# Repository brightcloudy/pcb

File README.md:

# pcb
Some OSHW PCBs that I have designed/am designing.

* zipscripts - Scripts built to zip up KiCad gerbers for tools such as gerblook.

* vna-steps - Boards designed to step up in complexity towards the modules required for the full 1 GHz VNA.
  * slowdds - AD9833 + STM32F030 based DDS module requiring external UART adapter.

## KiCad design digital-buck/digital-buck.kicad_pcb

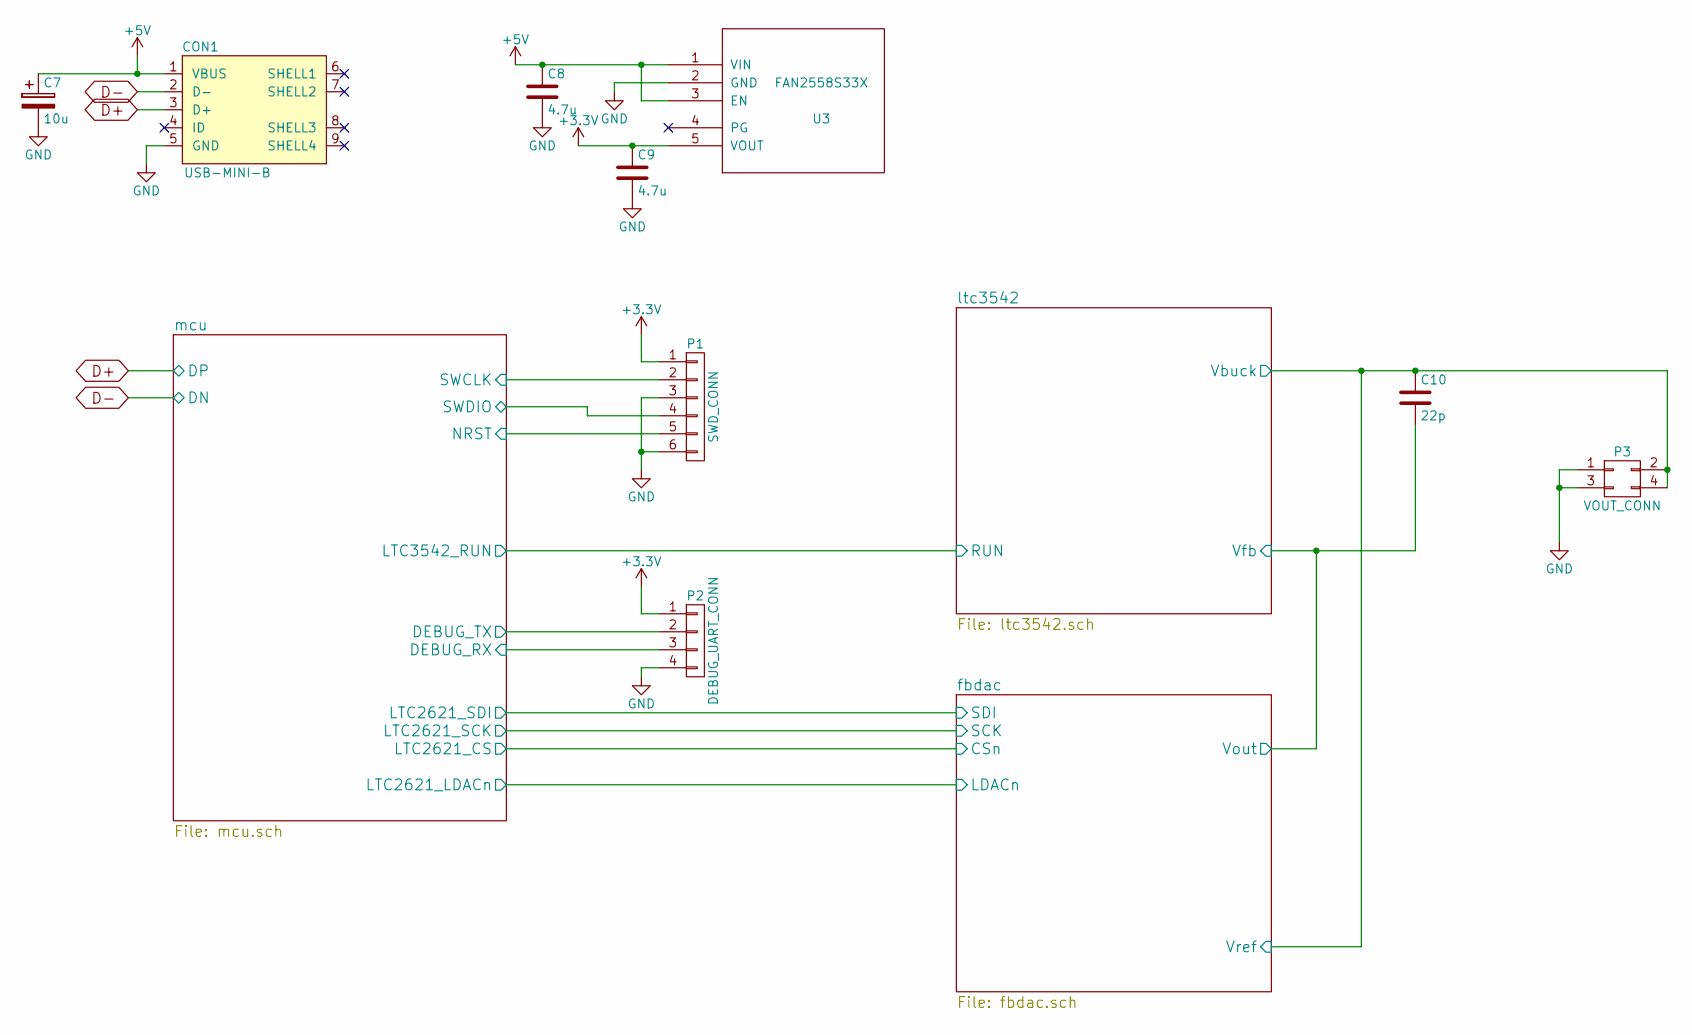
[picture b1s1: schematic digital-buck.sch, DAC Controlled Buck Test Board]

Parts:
C7: 10u; TantalC_SizeA_EIA-3216_Reflow
C8, C9: 4.7u; C_0603
C10: 22p; C_0603
CON1: USB-MINI-B; USB_Mini-B
P1: SWD_CONN; Pin_Header_Straight_1x06
P2: DEBUG_UART_CONN; Pin_Header_Straight_1x04
P3: VOUT_CONN; Pin_Header_Straight_2x02
U3: FAN2558S33X; SOT-23-5

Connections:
+3V3: C9.1, P1.1, P2.1, U3.5 (VOUT); also elsewhere on the board
+5V: C7.1, C8.1, CON1.1 (VBUS), U3.1 (VIN), U3.3 (EN); also elsewhere on the board
/ltc3542/Vbuck: C10.1, P3.2, P3.4; also elsewhere on the board
/ltc3542/Vfb: C10.2; also elsewhere on the board
/mcu/DEBUG_RX: P2.3; also elsewhere on the board
/mcu/DEBUG_TX: P2.2; also elsewhere on the board
/mcu/NRST: P1.5; also elsewhere on the board
/mcu/SWCLK: P1.2; also elsewhere on the board
/mcu/SWDIO: P1.4; also elsewhere on the board
D+: CON1.3 (D+); also elsewhere on the board
D-: CON1.2 (D-); also elsewhere on the board
GND: C7.2, C8.2, C9.2, CON1.5 (GND), P1.3, P1.6, P2.4, P3.1, P3.3, U3.2 (GND); also elsewhere on the board

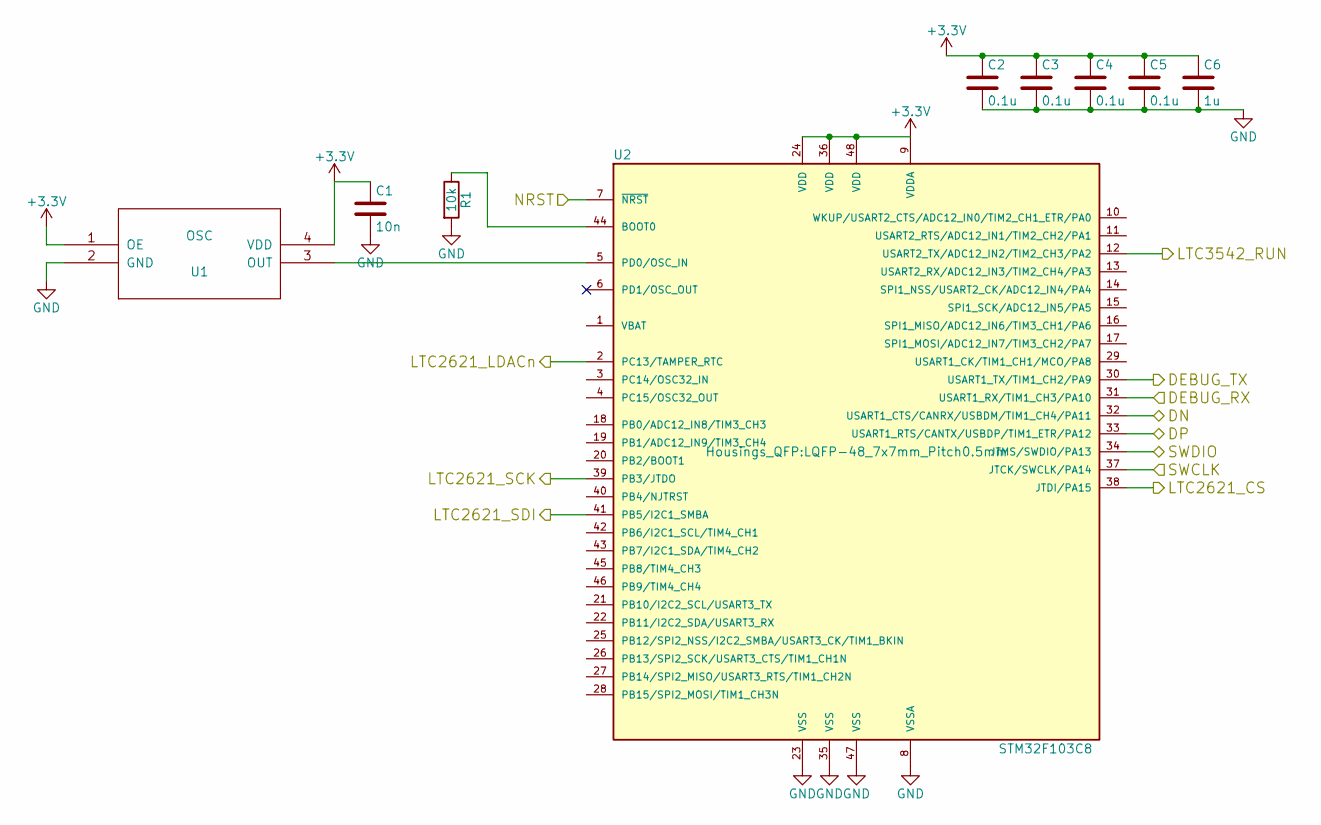
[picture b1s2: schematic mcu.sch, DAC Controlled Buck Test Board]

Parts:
C1: 10n; C_0402
C2, C3, C4, C5: 0.1u; C_0402
C6: 1u; C_0402
R1: 10k; R_0402
U1: OSC; SIOSC
U2: STM32F103C8; LQFP-48_7x7mm_Pitch0.5mm

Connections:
+3V3: C1.1, C2.1, C3.1, C4.1, C5.1, C6.1, U1.1 (OE), U1.4 (VDD), U2.9 (VDDA), U2.24 (VDD), U2.36 (VDD), U2.48 (VDD); also elsewhere on the board
/fbdac/CSn: U2.38 (JTDI/PA15); also elsewhere on the board
/fbdac/LDACn: U2.2 (PC13/TAMPER_RTC); also elsewhere on the board
/mcu/DEBUG_RX: U2.31 (USART1_RX/TIM1_CH3/PA10); also elsewhere on the board
/mcu/DEBUG_TX: U2.30 (USART1_TX/TIM1_CH2/PA9); also elsewhere on the board
/mcu/LTC2621_SCK: U2.39 (PB3/JTDO); also elsewhere on the board
/mcu/LTC2621_SDI: U2.41 (PB5/I2C1_SMBA); also elsewhere on the board
/mcu/LTC3542_RUN: U2.12 (USART2_TX/ADC12_IN2/TIM2_CH3/PA2); also elsewhere on the board
/mcu/NRST: U2.7 (~NRST); also elsewhere on the board
/mcu/SWCLK: U2.37 (JTCK/SWCLK/PA14); also elsewhere on the board
/mcu/SWDIO: U2.34 (JTMS/SWDIO/PA13); also elsewhere on the board
D+: U2.33 (USART1_RTS/CANTX/USBDP/TIM1_ETR/PA12); also elsewhere on the board
D-: U2.32 (USART1_CTS/CANRX/USBDM/TIM1_CH4/PA11); also elsewhere on the board
GND: C1.2, C2.2, C3.2, C4.2, C5.2, C6.2, R1.2, U1.2 (GND), U2.8 (VSSA), U2.23 (VSS), U2.35 (VSS), U2.47 (VSS); also elsewhere on the board
unnamed: R1.1, U2.44 (BOOT0)
unnamed: U1.3 (OUT), U2.5 (PD0/OSC_IN)

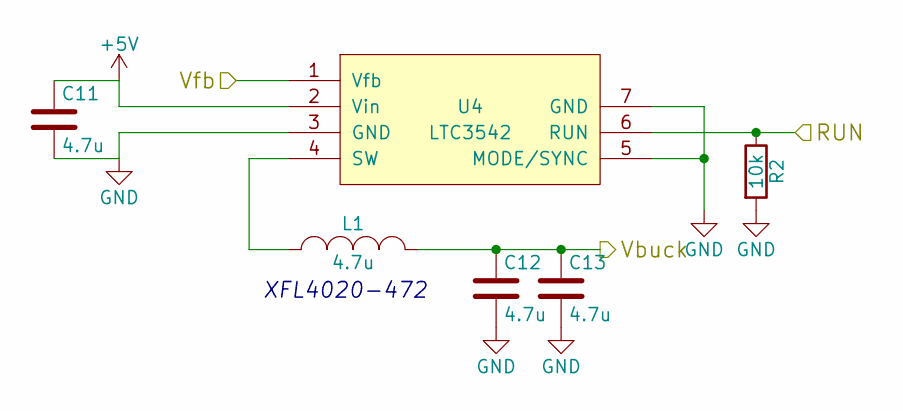
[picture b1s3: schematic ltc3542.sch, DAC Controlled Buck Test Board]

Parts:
C11, C12, C13: 4.7u; C_0603
L1: 4.7u; XFL4020
R2: 10k; R_0402
U4: LTC3542; DFN-6-1EP_2x2mm_Pitch0.5mm

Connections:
+5V: C11.1, U4.2 (Vin); also elsewhere on the board
/ltc3542/Vbuck: C12.1, C13.1, L1.2; also elsewhere on the board
/ltc3542/Vfb: U4.1 (Vfb); also elsewhere on the board
/mcu/LTC3542_RUN: R2.1, U4.6 (RUN); also elsewhere on the board
GND: C11.2, C12.2, C13.2, R2.2, U4.3 (GND), U4.5 (MODE/SYNC), U4.7 (GND); also elsewhere on the board
unnamed: L1.1, U4.4 (SW)

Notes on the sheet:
XFL4020-472

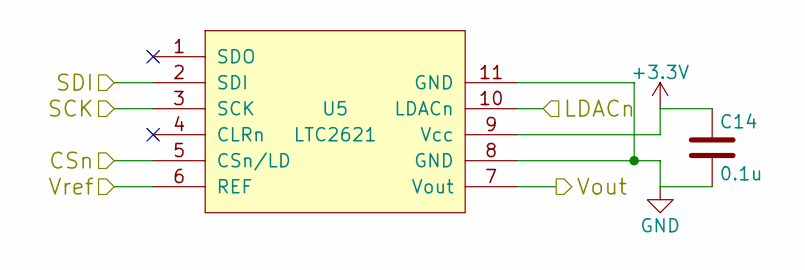
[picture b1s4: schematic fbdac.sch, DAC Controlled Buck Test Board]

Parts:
C14: 0.1u; C_0402
U5: LTC2621; DFN-10-1EP_3x3mm_Pitch0.5mm

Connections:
+3V3: C14.1, U5.9 (Vcc); also elsewhere on the board
/fbdac/CSn: U5.5 (CSn/LD); also elsewhere on the board
/fbdac/LDACn: U5.10 (LDACn); also elsewhere on the board
/ltc3542/Vbuck: U5.6 (REF); also elsewhere on the board
/ltc3542/Vfb: U5.7 (Vout); also elsewhere on the board
/mcu/LTC2621_SCK: U5.3 (SCK); also elsewhere on the board
/mcu/LTC2621_SDI: U5.2 (SDI); also elsewhere on the board
GND: C14.2, U5.8 (GND), U5.11 (GND); also elsewhere on the board

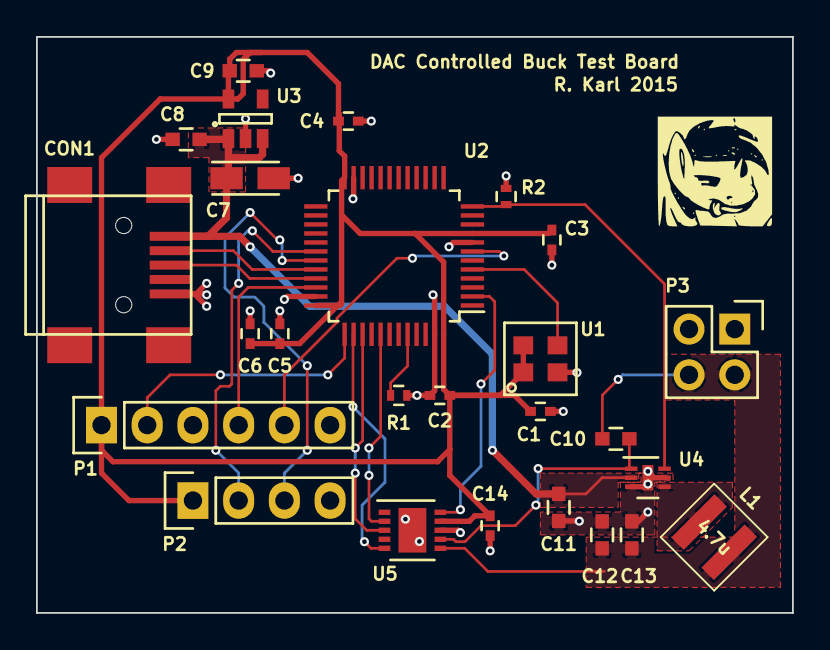
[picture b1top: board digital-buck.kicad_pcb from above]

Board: 2 copper layers, 42.0 x 32.0 mm, 26 parts (0 on the bottom side), 20 nets.

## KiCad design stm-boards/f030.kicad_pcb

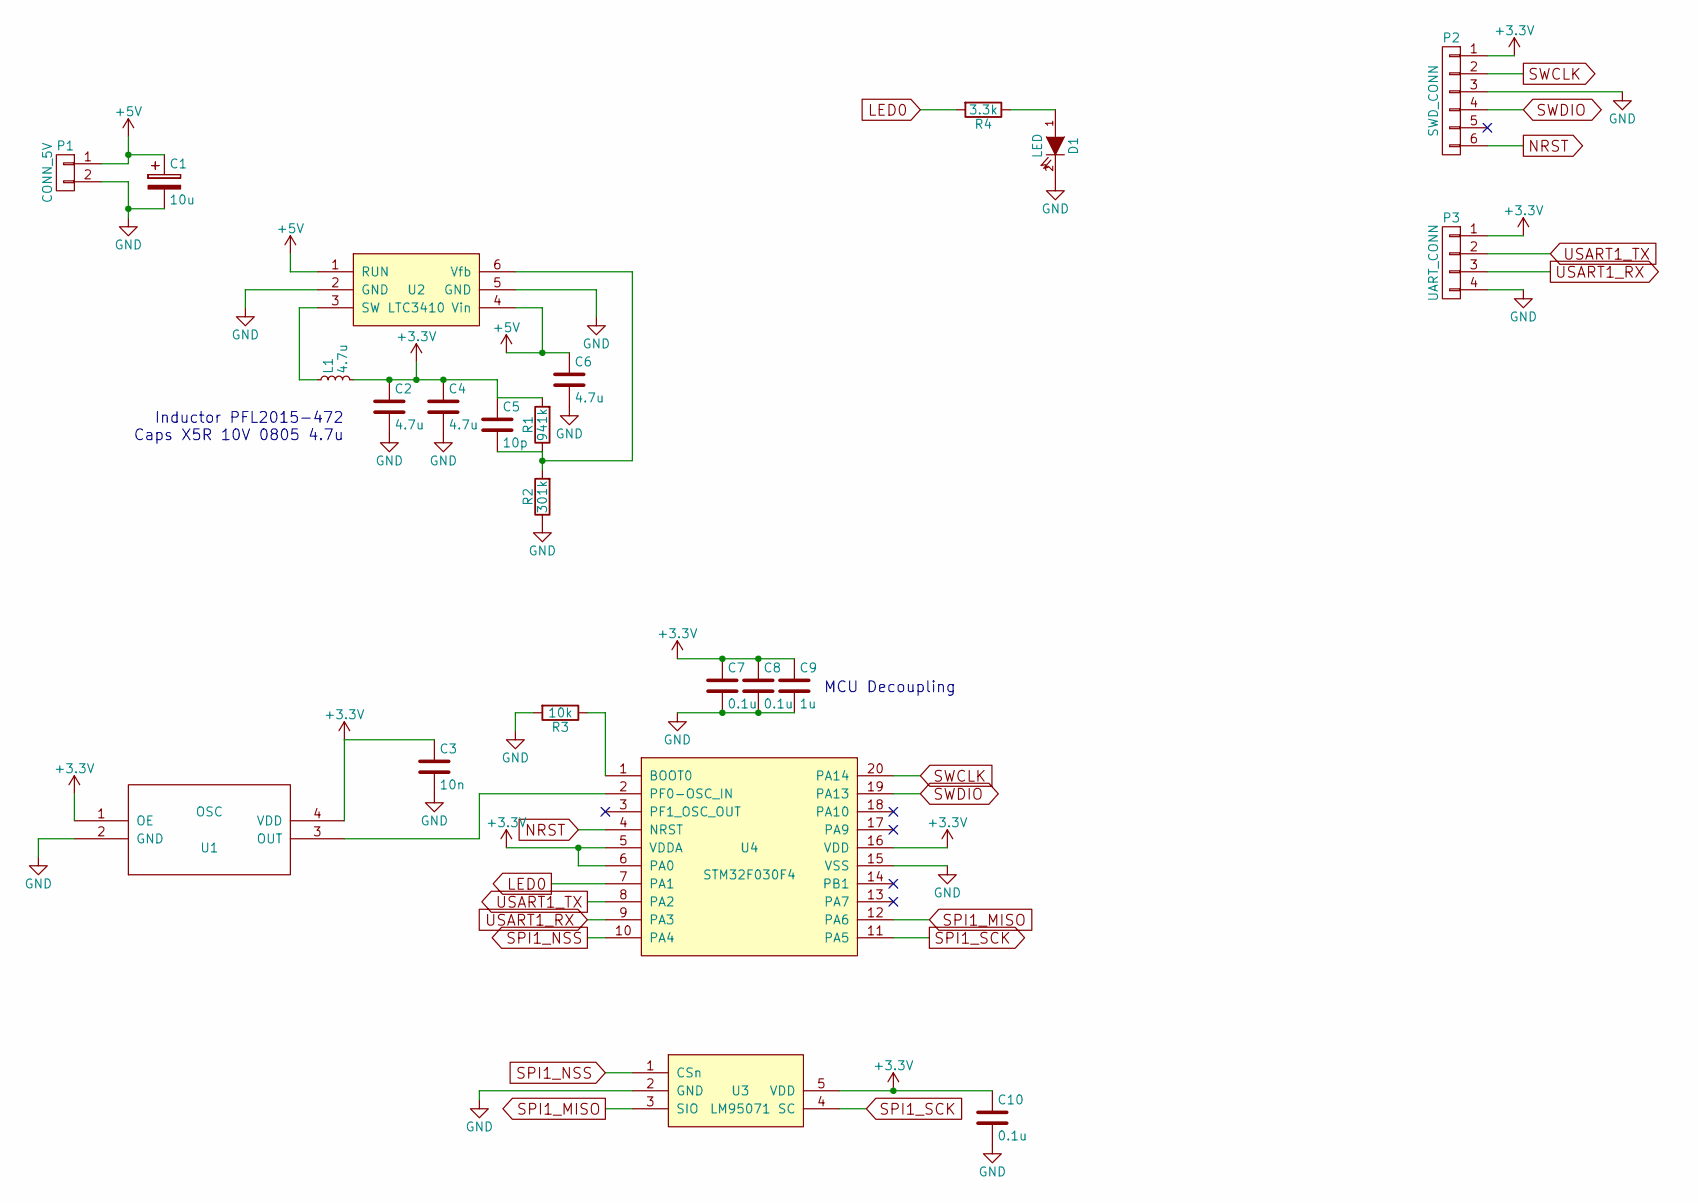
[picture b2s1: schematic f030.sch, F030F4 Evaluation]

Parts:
C1: 10u
C2, C4, C6: 4.7u
C3: 10n
C5: 10p
C7, C8, C10: 0.1u
C9: 1u
D1: LED
L1: 4.7u
P1: CONN_5V
P2: SWD_CONN
P3: UART_CONN
R1: 941k
R2: 301k
R3: 10k
R4: 3.3k
U1: OSC; MODULE
U2: LTC3410
U3: LM95071
U4: STM32F030F4

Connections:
+3V3: C2.1, C3.1, C4.1, C5.1, C7.1, C8.1, C9.1, C10.1, L1.2, P2.1, P3.1, R1.2, U1.1 (OE), U1.4 (VDD), U3.5 (VDD), U4.5 (VDDA), U4.6 (PA0), U4.16 (VDD)
+5V: C1.1, C6.1, P1.1, U2.1 (RUN), U2.4 (Vin)
GND: C1.2, C2.2, C3.2, C4.2, C6.2, C7.2, C8.2, C9.2, C10.2, D1.2 (K), P1.2, P2.3, P3.4, R2.1, R3.2, U1.2 (GND), U2.2 (GND), U2.5 (GND), U3.2 (GND), U4.15 (VSS)
LED0: R4.2, U4.7 (PA1)
NRST: P2.6, U4.4 (NRST)
unnamed: C5.2, R1.1, R2.2, U2.6 (Vfb)
unnamed: D1.1 (A), R4.1
unnamed: L1.1, U2.3 (SW)
unnamed: R3.1, U4.1 (BOOT0)
unnamed: U1.3 (OUT), U4.2 (PF0-OSC_IN)
SPI1_MISO: U3.3 (SIO), U4.12 (PA6)
SPI1_NSS: U3.1 (CSn), U4.10 (PA4)
SPI1_SCK: U3.4 (SC), U4.11 (PA5)
SWCLK: P2.2, U4.20 (PA14)
SWDIO: P2.4, U4.19 (PA13)
USART1_RX: P3.3, U4.9 (PA3)
USART1_TX: P3.2, U4.8 (PA2)

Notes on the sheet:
MCU Decoupling
Inductor PFL2015-472 Caps X5R 10V 0805 4.7u

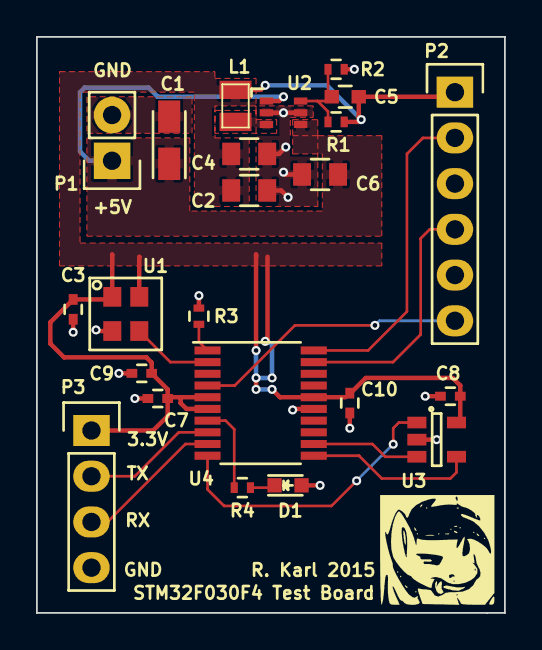
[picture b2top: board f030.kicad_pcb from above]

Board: 2 copper layers, 26.0 x 32.0 mm, 23 parts (0 on the bottom side), 17 nets.

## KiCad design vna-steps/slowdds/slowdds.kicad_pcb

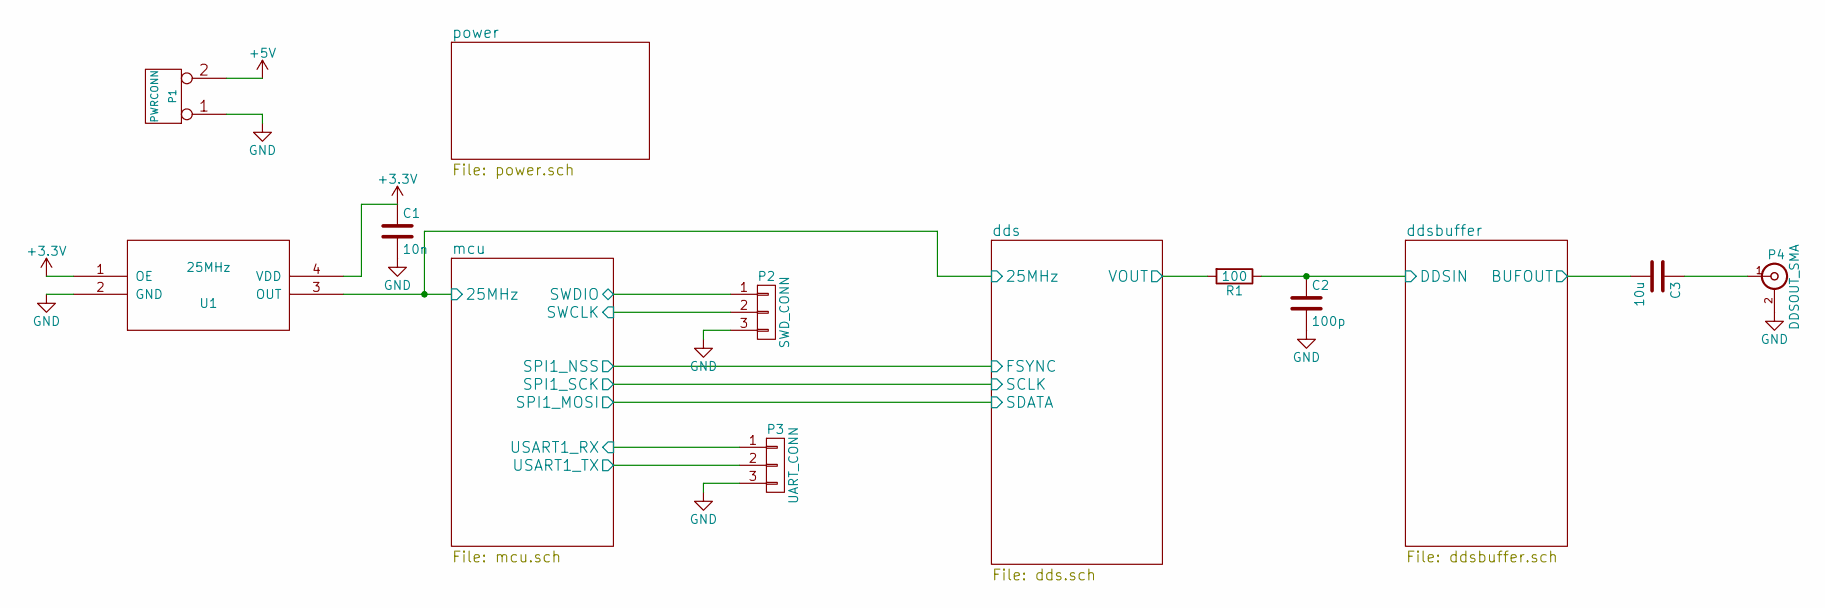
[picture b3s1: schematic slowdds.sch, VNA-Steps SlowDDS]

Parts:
C1: 10n; C_0402
C2: 100p; C_0603
C3: 10u; C_0603
P1: PWRCONN; Pin_Header_Straight_1x02
P2: SWD_CONN; Pin_Header_Straight_1x03
P3: UART_CONN; Pin_Header_Straight_1x03
P4: DDSOUT_SMA; sma_straight_32k101-400l5
R1: 100; R_0402
U1: 25MHz; SIOSC

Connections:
+3V3: C1.1, U1.1 (OE), U1.4 (VDD); also elsewhere on the board
+5V: P1.2 (PM); also elsewhere on the board
/dds/25MHz: U1.3 (OUT); also elsewhere on the board
/dds/VOUT: R1.2; also elsewhere on the board
/ddsbuffer/BUFOUT: C3.2; also elsewhere on the board
/ddsbuffer/DDSIN: C2.1, R1.1; also elsewhere on the board
/mcu/SWCLK: P2.2; also elsewhere on the board
/mcu/SWDIO: P2.1; also elsewhere on the board
/mcu/USART1_RX: P3.1; also elsewhere on the board
/mcu/USART1_TX: P3.2; also elsewhere on the board
GND: C1.2, C2.2, P1.1, P2.3, P3.3, P4.2 (Ext), U1.2 (GND); also elsewhere on the board
unnamed: C3.1, P4.1 (In)

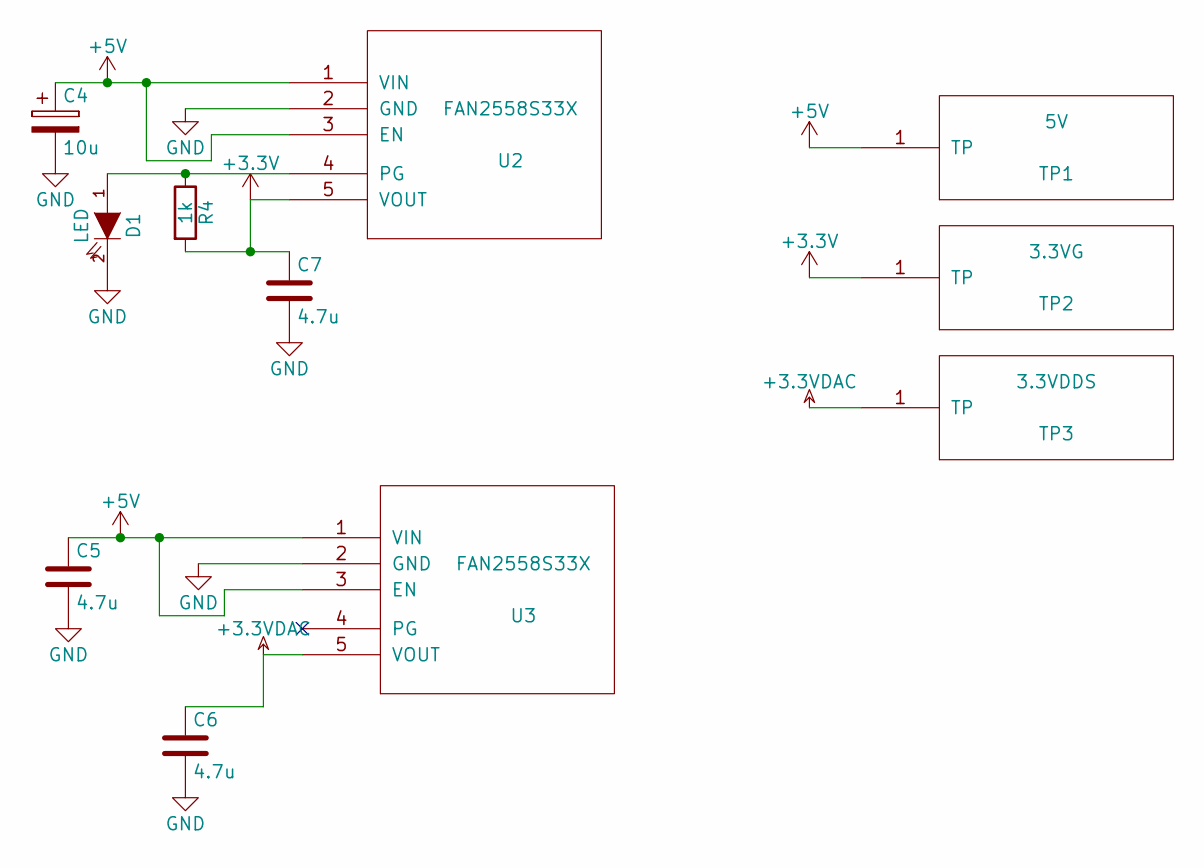
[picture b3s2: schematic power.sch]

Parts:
C4: 10u; TantalC_SizeA_EIA-3216_Reflow
C5, C6, C7: 4.7u; C_0603
D1: LED; LED-0603
R4: 1k; R_0402
TP1: 5V; TP
TP2: 3.3VG; TP
TP3: 3.3VDDS; TP
U2, U3: FAN2558S33X; SOT-23-5

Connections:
+3.3VDAC: C6.1, TP3.1, U3.5 (VOUT); also elsewhere on the board
+3V3: C7.1, R4.2, TP2.1, U2.5 (VOUT); also elsewhere on the board
+5V: C4.1, C5.1, TP1.1, U2.1 (VIN), U2.3 (EN), U3.1 (VIN), U3.3 (EN); also elsewhere on the board
GND: C4.2, C5.2, C6.2, C7.2, D1.2 (K), U2.2 (GND), U3.2 (GND); also elsewhere on the board
unnamed: D1.1 (A), R4.1, U2.4 (PG)

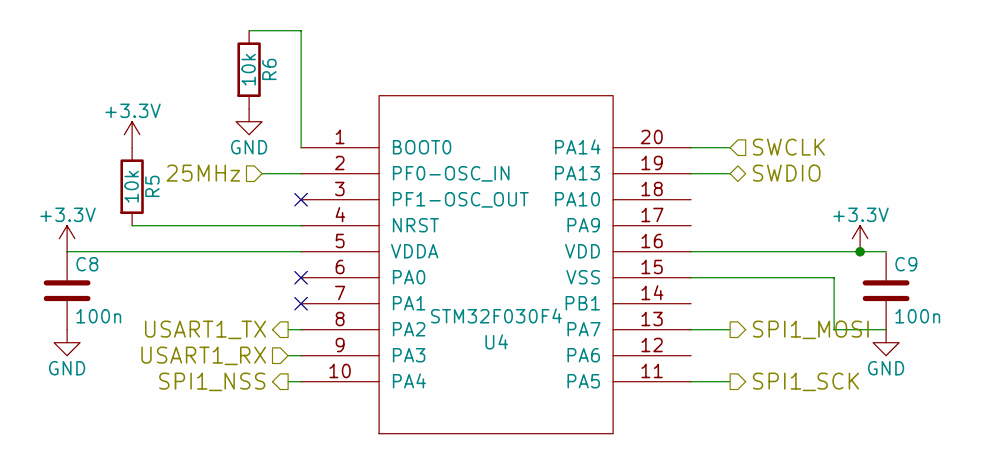
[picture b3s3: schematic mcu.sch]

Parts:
C8, C9: 100n; C_0402
R5, R6: 10k; R_0402
U4: STM32F030F4; TSSOP-20_4.4x6.5mm_Pitch0.65mm

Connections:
+3V3: C8.1, C9.1, R5.1, U4.5 (VDDA), U4.16 (VDD); also elsewhere on the board
/dds/25MHz: U4.2 (PF0-OSC_IN); also elsewhere on the board
/dds/FSYNC: U4.10 (PA4); also elsewhere on the board
/dds/SCLK: U4.11 (PA5); also elsewhere on the board
/dds/SDATA: U4.13 (PA7); also elsewhere on the board
/mcu/SWCLK: U4.20 (PA14); also elsewhere on the board
/mcu/SWDIO: U4.19 (PA13); also elsewhere on the board
/mcu/USART1_RX: U4.9 (PA3); also elsewhere on the board
/mcu/USART1_TX: U4.8 (PA2); also elsewhere on the board
GND: C8.2, C9.2, R6.2, U4.15 (VSS); also elsewhere on the board
unnamed: R5.2, U4.4 (NRST)
unnamed: R6.1, U4.1 (BOOT0)

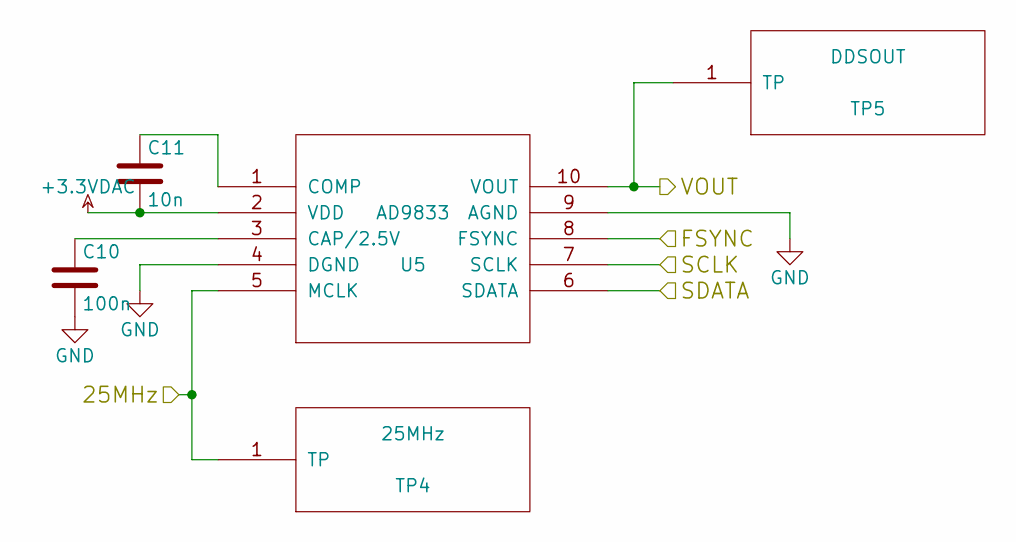
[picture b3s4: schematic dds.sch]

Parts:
C10: 100n; C_0402
C11: 10n; C_0402
TP4: 25MHz; TP
TP5: DDSOUT; TP
U5: AD9833; MSOP-10_3x3mm_Pitch0.5mm

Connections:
+3.3VDAC: C11.2, U5.2 (VDD); also elsewhere on the board
/dds/25MHz: TP4.1, U5.5 (MCLK); also elsewhere on the board
/dds/FSYNC: U5.8 (FSYNC); also elsewhere on the board
/dds/SCLK: U5.7 (SCLK); also elsewhere on the board
/dds/SDATA: U5.6 (SDATA); also elsewhere on the board
/dds/VOUT: TP5.1, U5.10 (VOUT); also elsewhere on the board
GND: C10.2, U5.4 (DGND), U5.9 (AGND); also elsewhere on the board
unnamed: C10.1, U5.3 (CAP/2.5V)
unnamed: C11.1, U5.1 (COMP)

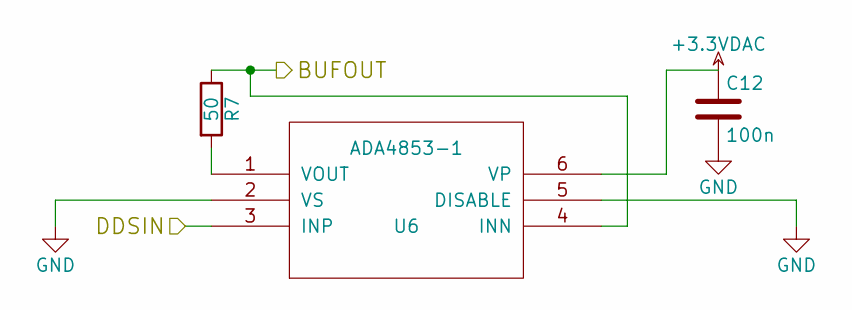
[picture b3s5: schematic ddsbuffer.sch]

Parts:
C12: 100n; C_0402
R7: 50; R_0603
U6: ADA4853-1; SC-70-6

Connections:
+3.3VDAC: C12.1, U6.6 (VP); also elsewhere on the board
/ddsbuffer/BUFOUT: R7.1, U6.4 (INN); also elsewhere on the board
/ddsbuffer/DDSIN: U6.3 (INP); also elsewhere on the board
GND: C12.2, U6.2 (VS), U6.5 (DISABLE); also elsewhere on the board
unnamed: R7.2, U6.1 (VOUT)

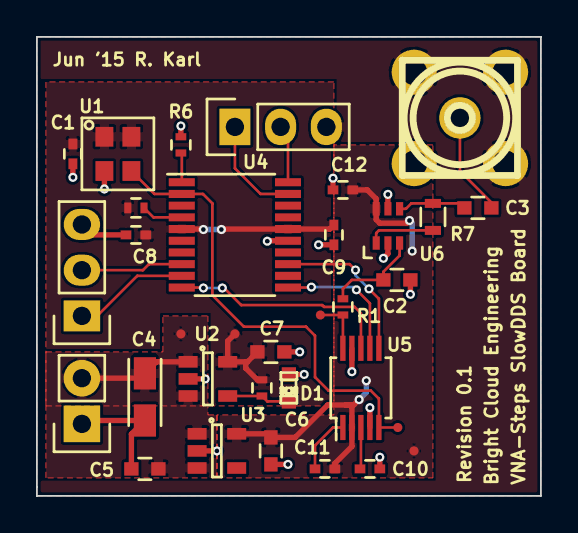
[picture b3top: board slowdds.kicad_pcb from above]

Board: 2 copper layers, 28.0 x 25.5 mm, 33 parts (0 on the bottom side), 22 nets.

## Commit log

2015-06-20 Add .bak files to gitignore. Add schematic for VNA Steps slowdds.
2015-06-20 Generate netlist and run cvpcb.
2015-06-20 slowdds layout completed. images + schematics generated. ZIP file scripts added and documented in README. slowdds gerbers generated + zipped.
2015-06-20 Add README to slowdds + update gitignore for autosaves
2015-06-20 Fix slowdds README image path
2015-06-21 Add design document specification for USB power stick.
2015-06-22 Update docs for USB PSU
2015-07-06 Add specification for the buck controller on the USB PSU.
2015-07-08 cry myself to sleep
2015-07-09 Add design doc for USB power meter + condom.
2015-07-10 vacay
2015-12-02 Completed two new boards and WIP one.
